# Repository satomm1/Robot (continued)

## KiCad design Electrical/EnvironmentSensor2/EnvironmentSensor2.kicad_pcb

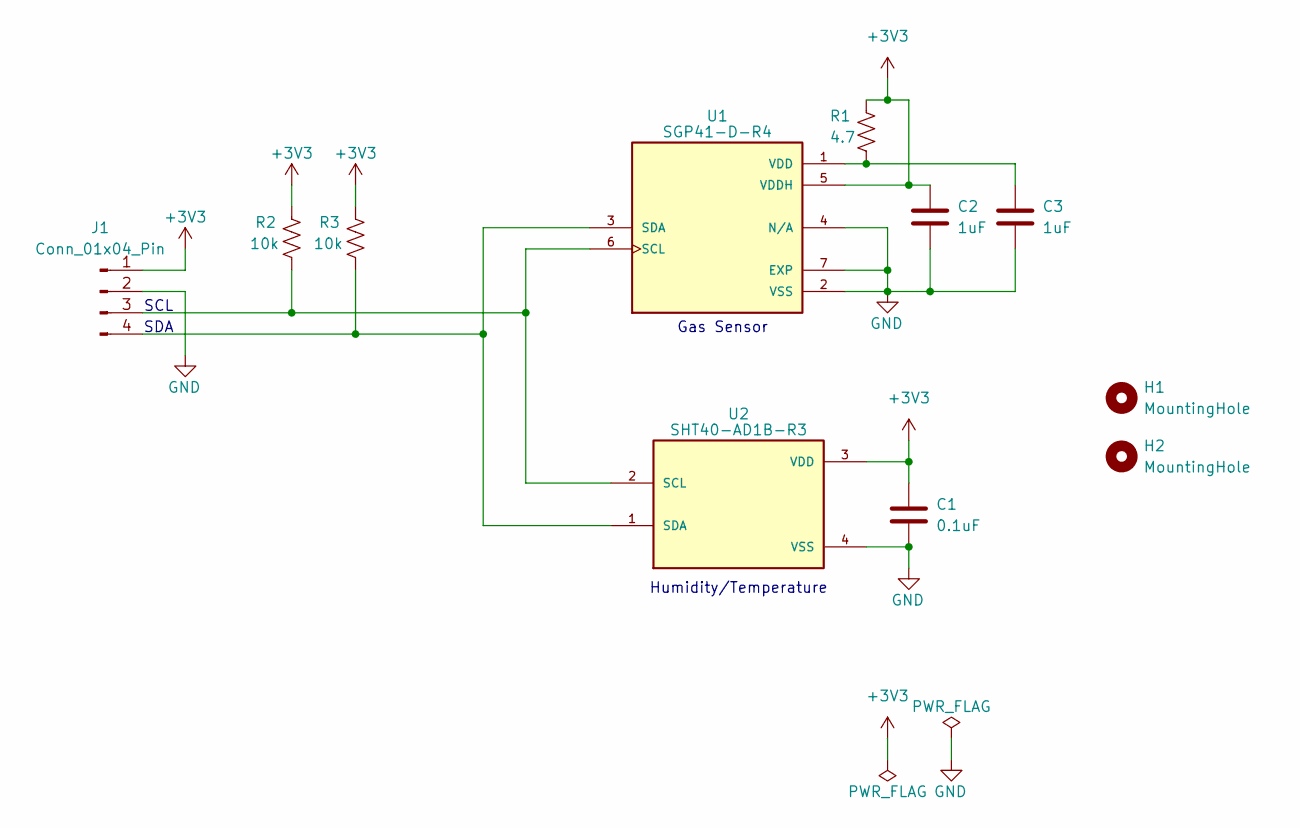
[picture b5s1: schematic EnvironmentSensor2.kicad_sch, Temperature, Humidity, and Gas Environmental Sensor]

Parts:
C1: 0.1uF; C_0805_2012Metric_Pad1.18x1.45mm_HandSolder; Mfr P/N CL21B104KBCNNNC
C2, C3: 1uF; C_0805_2012Metric_Pad1.18x1.45mm_HandSolder; Mfr P/N 1276-1066-1-ND
H1, H2: MountingHole; MountingHole_3.2mm_M3
J1: Conn_01x04_Pin; Molex_PicoBlade_53048-0410_1x04_P1.25mm_Horizontal; Mfr P/N 0530480410
R1: 4.7; R_0805_2012Metric_Pad1.20x1.40mm_HandSolder; Mfr P/N RC0805FR-074R7L
R2, R3: 10k; R_0805_2012Metric_Pad1.20x1.40mm_HandSolder; Mfr P/N RMCF0805FT10K0
U1: SGP41-D-R4; XDCR_SGP41-D-R4; Mfr P/N SGP41-D-R4
U2: SHT40-AD1B-R3; SHT4X; Mfr P/N SHT40-AD1B-R3

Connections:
+3V3: C1.1, C2.1, J1.1, R1.1, R2.1, R3.1, U1.5 (VDDH), U2.3 (VDD)
GND: C1.2, C2.2, C3.2, J1.2, U1.2 (VSS), U1.4 (N/A), U1.7 (EXP), U2.4 (VSS)
unnamed: J1.3, R2.2, U1.6 (SCL), U2.2 (SCL)
unnamed: J1.4, R3.2, U1.3 (SDA), U2.1 (SDA)
unnamed: C3.1, R1.2, U1.1 (VDD)

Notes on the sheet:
SDA
Gas Sensor
Humidity/Temperature
SCL

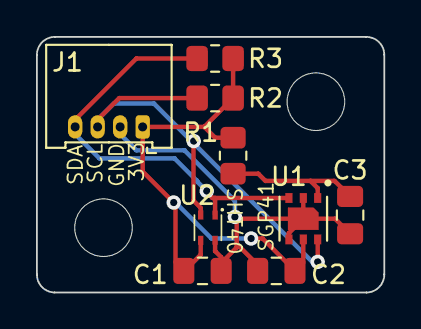
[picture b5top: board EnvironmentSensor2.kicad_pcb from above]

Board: 2 copper layers, 19.3 x 14.2 mm, 11 parts (0 on the bottom side), 5 nets.

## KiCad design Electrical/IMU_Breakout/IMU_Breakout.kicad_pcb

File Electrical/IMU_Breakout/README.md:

# 6-axis IMU

This directory contains the electrical schematic for a breakout board for the Bosch BMI323 6-axis IMU. This IMU provides a 16 bit digital triaxial accelerometer, a 16 bit digital triaxial gyroscope, and a 16 bit digital temperature sensor.

This breakout board is designed so that the IMU can be placed anywhere that is convenient.

## Soldering the IMU
This IMU is in a QFN package, which means the device should be reflow soldered. Alternatively, you can carefully apply solder to the PCB pads, put the IMU on top, and use a heat gun to solder the IMU.

## Pin directions
The header pins should be soldered on the bottom of the PCB:

## Installing the IMU
The assembly is meant to be installed on the robot with the IMU facing upwards. The positive X/Y/Z axes are designated on the board. The IMU should be connected via wire to the designated header on the main control board:

| IMU Breakout Pin | Main Control Board Connection |
|------------------|-------------------------------|
| 3V3              | 3.3V                          |
| GND              | GND                           |
| SCK              | SCK                           |
| CS               | CS                            |
| SDO              | SDI                           |
| SDI              | SDO                           |
| INT1             | INT1 (Currently Unused)       |
| INT2             | INT2 (Currently Unused)       |

The IMU connection on the main control board is indicated below:

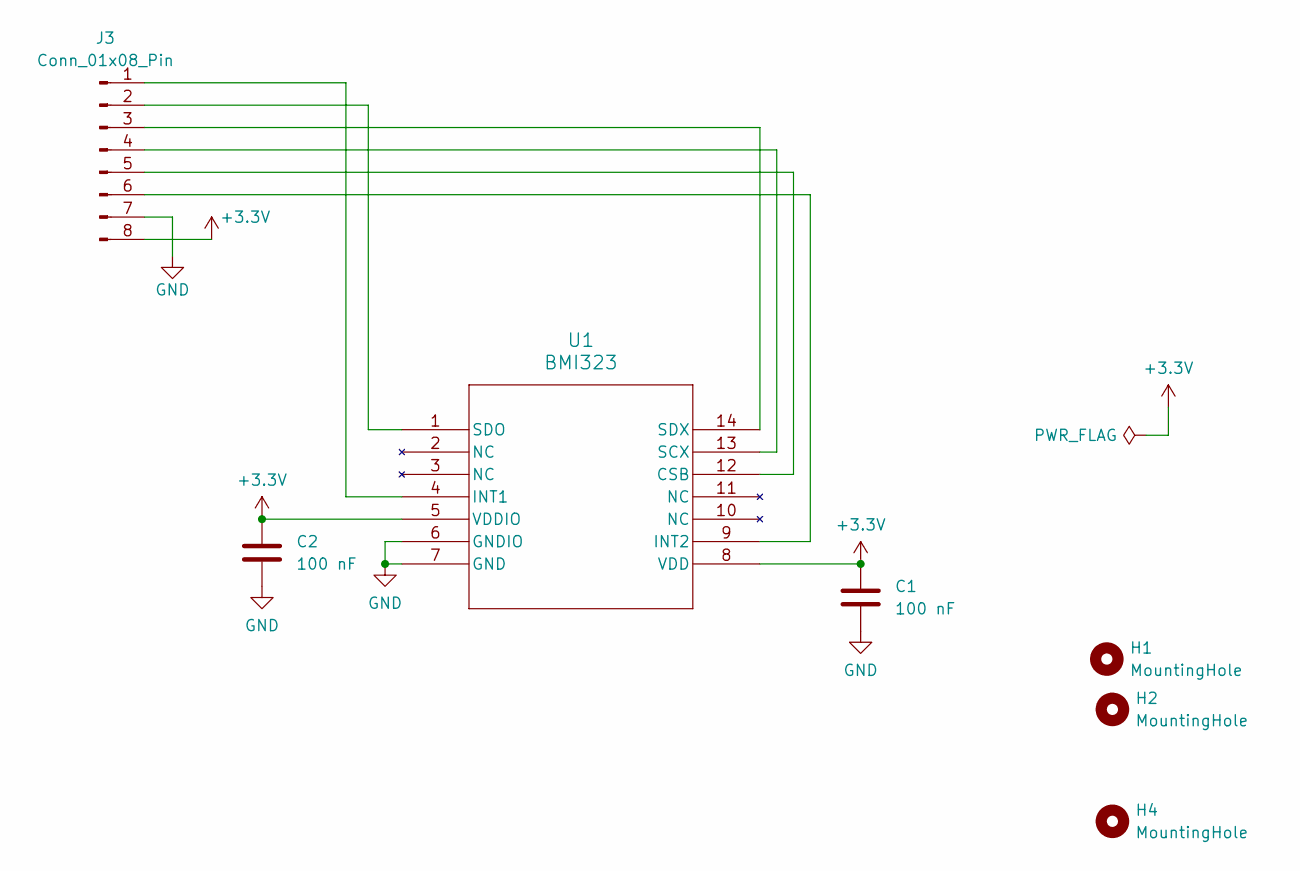
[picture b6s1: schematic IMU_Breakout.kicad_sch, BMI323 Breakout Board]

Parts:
C1, C2: 100 nF; C_0805_2012Metric_Pad1.18x1.45mm_HandSolder; Mfr P/N CL21B104KBCNNNC
H1, H2, H4: MountingHole; MountingHole_3.2mm_M3
J3: Conn_01x08_Pin; Molex_PicoBlade_53048-0810_1x08_P1.25mm_Horizontal; Mfr P/N 0530480810
U1: BMI323; BMI323_BOS-M; Mfr P/N BMI323

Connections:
+3.3V: C1.1, C2.1, J3.8, U1.5 (VDDIO), U1.8 (VDD)
GND: C1.2, C2.2, J3.7, U1.6 (GNDIO), U1.7 (GND)
unnamed: J3.1, U1.4 (INT1)
unnamed: J3.2, U1.1 (SDO)
unnamed: J3.3, U1.14 (SDX)
unnamed: J3.4, U1.13 (SCX)
unnamed: J3.5, U1.12 (CSB)
unnamed: J3.6, U1.9 (INT2)

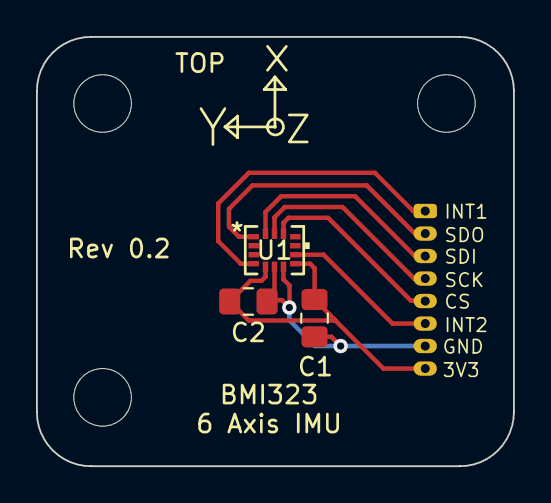
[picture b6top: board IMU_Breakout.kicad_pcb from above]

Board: 2 copper layers, 26.5 x 23.9 mm, 7 parts (1 on the bottom side), 8 nets.

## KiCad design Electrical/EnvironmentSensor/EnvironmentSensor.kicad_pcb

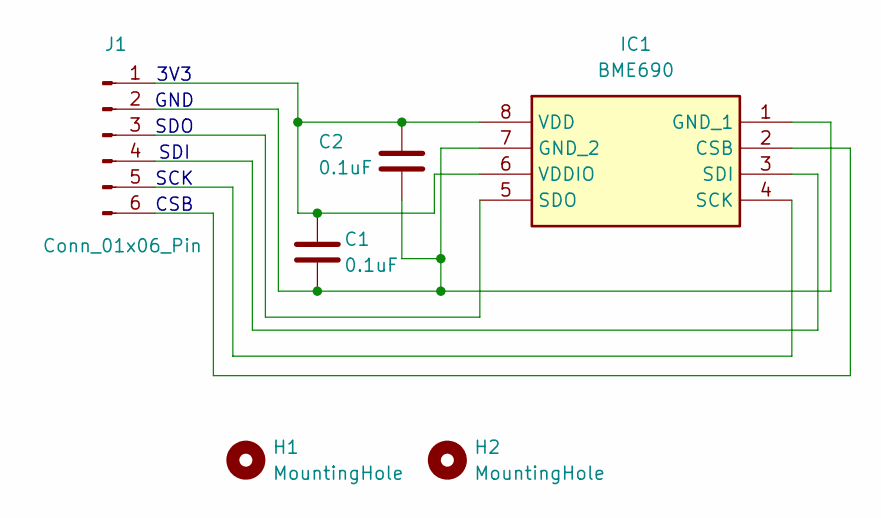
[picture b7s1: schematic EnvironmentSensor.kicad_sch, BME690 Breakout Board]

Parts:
C1, C2: 0.1uF; C_0805_2012Metric_Pad1.18x1.45mm_HandSolder; Mfr P/N CL21B104KBCNNNC
H1, H2: MountingHole; MountingHole_3.2mm_M3
IC1: BME690; Mouser Part Number 262-BME690
J1: Conn_01x06_Pin; Molex_PicoBlade_53048-0610_1x06_P1.25mm_Horizontal; Mfr P/N 0530480610

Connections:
unnamed: IC1.2 (CSB), J1.6
unnamed: C1.2, C2.2, IC1.1 (GND_1), IC1.7 (GND_2), J1.2
unnamed: IC1.4 (SCK), J1.5
unnamed: IC1.3 (SDI), J1.4
unnamed: IC1.5 (SDO), J1.3
unnamed: C1.1, C2.1, IC1.6 (VDDIO), IC1.8 (VDD), J1.1

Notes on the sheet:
GND
SDI
CSB
SDO
3V3
SCK

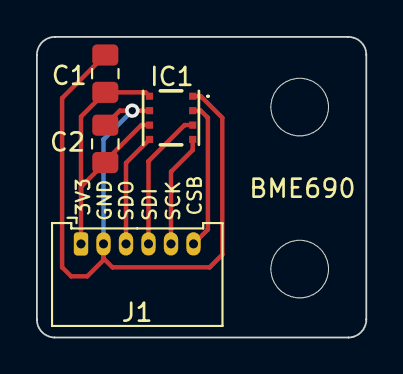
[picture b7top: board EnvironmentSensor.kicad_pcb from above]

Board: 2 copper layers, 18.3 x 16.7 mm, 6 parts (0 on the bottom side), 6 nets.

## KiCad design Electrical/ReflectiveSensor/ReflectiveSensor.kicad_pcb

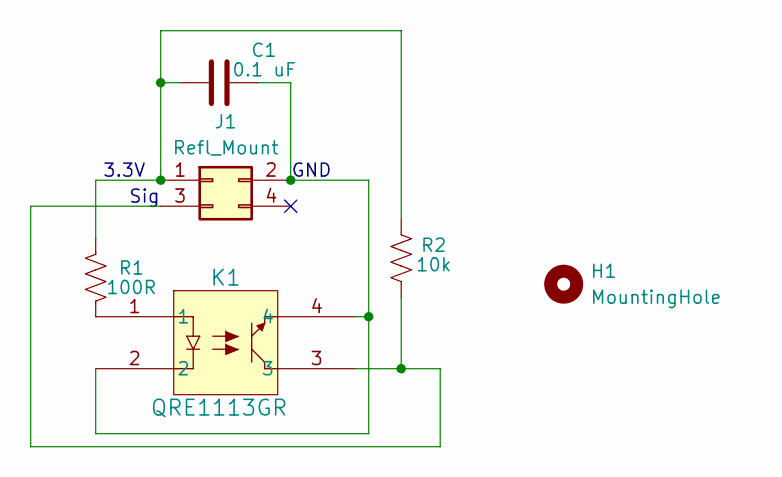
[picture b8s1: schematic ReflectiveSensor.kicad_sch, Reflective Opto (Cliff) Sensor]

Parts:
C1: 0.1 uF; C_0805_2012Metric_Pad1.18x1.45mm_HandSolder; Mfr P/N CL21B104KBCNNNC
H1: MountingHole; MountingHole_2.2mm_M2
J1: Refl_Mount; PinHeader_2x02_P2.54mm_Vertical
K1: QRE1113GR; ARUSM-313_100CY_FAS-M; Mfr P/N QRE1113GR
R1: 100R; R_0805_2012Metric_Pad1.20x1.40mm_HandSolder; Mfr P/N RMCF0805FT100R
R2: 10k; R_0805_2012Metric_Pad1.20x1.40mm_HandSolder; Mfr P/N RMCF0805FT10K0

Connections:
unnamed: C1.1, J1.1, R1.2, R2.2
unnamed: C1.2, J1.2, K1.2, K1.4
unnamed: J1.3, K1.3, R2.1
unnamed: K1.1, R1.1

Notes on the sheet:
GND
Sig
3.3V

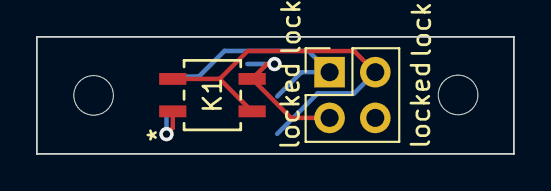
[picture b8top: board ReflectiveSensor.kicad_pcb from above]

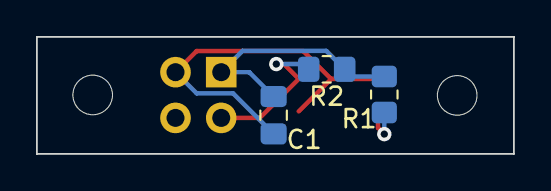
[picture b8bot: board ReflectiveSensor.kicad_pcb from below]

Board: 2 copper layers, 26.5 x 6.5 mm, 7 parts (3 on the bottom side), 4 nets.

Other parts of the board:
H2: MountingHole; MountingHole_2.2mm_M2

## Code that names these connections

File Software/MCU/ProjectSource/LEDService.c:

/****************************************************************************
 Module
   LEDService.c

 Revision
   1.0.1

 Description
   This is a file for implementing the LED service under the
   Gen2 Events and Services Framework.

 Notes

 History
 When           Who     What/Why
 -------------- ---     --------

****************************************************************************/
/*----------------------------- Include Files -----------------------------*/
/* include header files for this state machine as well as any machines at the
   next lower level in the hierarchy that are sub-machines to this machine
*/
#include "ES_Configure.h"
#include "ES_Framework.h"
#include "LEDService.h"

/*----------------------------- Module Defines ----------------------------*/

/*---------------------------- Module Functions ---------------------------*/
/* prototypes for private functions for this service.They should be functions
   relevant to the behavior of this service
*/

/*---------------------------- Module Variables ---------------------------*/
// with the introduction of Gen2, we need a module level Priority variable
static uint8_t MyPriority;

/*------------------------------ Module Code ------------------------------*/
/****************************************************************************
 Function
     InitLEDService

 Parameters
     uint8_t : the priorty of this service

 Returns
     bool, false if error in initialization, true otherwise

 Description
     Saves away the priority, and does any
     other required initialization for this service
****************************************************************************/
bool InitLEDService(uint8_t Priority)
{
  ES_Event_t ThisEvent;

  MyPriority = Priority;
  
  // Set LED pins to digital output
  TRISCCLR = _TRISC_TRISC12_MASK | _TRISC_TRISC15_MASK;
  TRISHCLR = _TRISH_TRISH4_MASK | _TRISH_TRISH5_MASK | _TRISH_TRISH6_MASK | _TRISH_TRISH7_MASK;
  
  ANSELHCLR = _ANSELH_ANSH4_MASK | _ANSELH_ANSH5_MASK | _ANSELH_ANSH6_MASK;
  
  // Start with all LEDs turned off
  LATHbits.LATH4 = 0; // LED2
  LATHbits.LATH5 = 0; // LED1
  LATHbits.LATH6 = 0; // LED4
  LATHbits.LATH7 = 0; // LED3
  LATCbits.LATC12 = 0; // LED6
  LATCbits.LATC15 = 0; // LED5
  
  // post the initial transition event
  ThisEvent.EventType = ES_INIT;
  if (ES_PostToService(MyPriority, ThisEvent) == true)
  {
    return true;
  }
  else
  {
    return false;
  }
}

/****************************************************************************
 Function
     PostLEDService

 Parameters
     EF_Event_t ThisEvent ,the event to post to the queue

 Returns
     bool false if the Enqueue operation failed, true otherwise

 Description
     Posts an event to this state machine's queue
****************************************************************************/
bool PostLEDService(ES_Event_t ThisEvent)
{
  return ES_PostToService(MyPriority, ThisEvent);
}

/****************************************************************************
 Function
    RunLEDService

 Parameters
   ES_Event_t : the event to process

 Returns
   ES_Event, ES_NO_EVENT if no error ES_ERROR otherwise

 Description
   Turns LEDs on or off
****************************************************************************/
ES_Event_t RunLEDService(ES_Event_t ThisEvent)
{
  ES_Event_t ReturnEvent;
  ReturnEvent.EventType = ES_NO_EVENT; // assume no errors
  
  switch (ThisEvent.EventType) {
      
      // Turn a LED on
      case EV_LED_ON:
      {
          // Event Parameter is the LED to turn on
          switch (ThisEvent.EventParam) {
              case 1:
              {
                  LATHbits.LATH5 = 1;
              }
              break;
              
              case 2:
              {
                  LATHbits.LATH4 = 1;
              }
              break;
              
              case 3:
              {
                  LATHbits.LATH7 = 1;
              }
              break;
              
              case 4:
              {
                  LATHbits.LATH6 = 1;
              }
              break;
              
              case 5:
              {
                  LATCbits.LATC15 = 1;
              }
              break;
              
              case 6:
              {
                  LATCbits.LATC12 = 1;
              }
              break;
              
              default:
                break;
          }
      }
      break;
      
      // Turn a LED off
      case EV_LED_OFF:
      {
          // Event Parameter is the LED to turn off
          switch (ThisEvent.EventParam) {
              case 1:
              {
                  LATHbits.LATH5 = 0;
              }
              break;
              
              case 2:
              {
                  LATHbits.LATH4 = 0;
              }
              break;
              
              case 3:
              {
                  LATHbits.LATH7 = 0;
              }
              break;
              
              case 4:
              {
                  LATHbits.LATH6 = 0;
              }
              break;
              
              case 5:
              {
                  LATCbits.LATC15 = 0;
              }
              break;
              
              case 6:
              {
                  LATCbits.LATC12 = 0;
              }
              break;
              
              default:
                break;
          }
      }
      break;
      
      default:
        break;
  }
    
  return ReturnEvent;
}

/***************************************************************************
 private functions
 ***************************************************************************/

/*------------------------------- Footnotes -------------------------------*/
/*------------------------------ End of file ------------------------------*/

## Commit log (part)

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2023-11-08 Add initial directories and READMEs
2023-11-08 Update KiCAD format
2023-11-11 Add the majority of the electronics
2023-11-13 Begin layout of pcb
2023-11-16 First Pass at the routing
2023-11-25 Some finishing touches to the board
2023-11-25 Add a bom and initial mechanical drawings
2023-11-25 Finalize Reflective Opto Sensor
2023-11-26 Add some final touches
2023-11-27 Resize the reflective sensor
2023-11-27 Add updated robot design
2023-11-29 Add Robot Summary Document
2023-11-30 Finish final board design for Rev 0.1 Main board and reflective Sensor. Created Gerbers.
2023-12-01 Add initial PIC32 Framework Code
2023-12-20 Add starter code for the IMU and Motor Control state machines
2023-12-28 Add some code for communicating between ros and MCU
2023-12-29 Add button debouncers and add more motor control
2024-01-08 Dead reckoning and IMU
2024-01-09 Sort out some of the details for jetson-MCU comms and do some more motor code
2024-01-10 Fully align ROS python code with MCU for spi transfer
2024-01-10 Add a service to turn LEDs on or off
2024-01-11 Modify the spi comms file
2024-01-11 Made a comment that we may need a small resistor to draw some current from battery to keep on
2024-01-19 updated model
2024-01-20 Add bom for reflective sensor pcb
2024-01-20 Add backups
2024-01-23 Backups
2024-01-23 Add updates
2024-01-24 Begin the debugging process. Know LEDs and USB-UART are working here
2024-01-26 Get most services at least functioning without crashing
2024-01-26 Confirm button debouncers/state machines work
2024-01-26 Add code for basic motor testing
2024-01-28 Get PI control mostly working
2024-01-29 Updates to robot upper level design
2024-01-29 Get SPI between jetson and mcu figured out
2024-01-31 Implement Jetson comm functionality for dead reckoning and position
2024-02-02 Just making more progress...
2024-02-02 Add IMU breakout board design
2024-02-02 Made V0.2 revisions to Main Board
2024-02-05 Directly write to SPI2BUF instead of passing it as an argument
2024-02-06 Change limits on maximum velocities
2024-02-07 Change molex+terminal block to just 6 position molex for the motor/encoder terminal
2024-02-07 Center the IMU
2024-02-08 Update dead reckoning update to occur at 50 Hz rate, also update base width of robot
2024-02-09 just some backups
2024-02-14 Change some spi stuff with jetson, probably will need to revert
2024-02-14 Revert "Change some spi stuff with jetson, probably will need to revert"
    This reverts commit 06b93681a91bff43f5faf43f78ca409b5d33d08e.
    Revert back to PI control instead of PID
2024-02-14 Change to PID control
2024-02-14 Allocate 16 bytes for the receiveBuffer-- May have been causing the problem of data getting misaligned with jetson
2024-03-08 MPLAB xml file
2024-03-10 Finalize IMU Breakout board
2024-03-10 Finalize rev 0.2
2024-03-10 Add V0.2 to archive
2024-03-11 Dead reckoning use exact formula, increase rate at which dead reckoning is calculated
2024-03-11 further reduce update time for dead reckoning calcs
2024-03-21 Add file for testing IMU
2024-03-21 Begin adding new initialization code for BMI IMU
2024-03-23 Add code for testing ADC, should be good now just need to debug
2024-04-02 Edit imu code
2024-04-02 Finalize code for setting up IMU and verifying soldering is correct
2024-04-07 Get code for IMU working
2024-04-08 Get ADC test code working
2024-04-08 Integrate ADC/Reflect service with Jetson messaging
2024-04-10 Add new details to the bringup document
2024-04-10 Add updated components
2024-04-22 Add minimally working docker files for running Kafka/Zookeeper
2024-04-22 Make some useful comments in a README
2024-05-03 Add IMU capability for REV 0.1 board
2024-05-03 Finish debugging new IMU setup
2024-05-06 Add functionality to easily switch between the different encoders
2024-05-24 Add ability to query the fault status of the two motor drivers
2024-07-26 Estimate orienation using Madgwick filter from IMU
2024-07-26 Give document for docker container setup
2024-08-16 Begin adding code fo rEEPORM and RL
2024-08-16 Add some bringup instructions
2024-08-20 Tune parameters in Motor and fix small issues
2024-10-28 Add button data to info sent to Jetson
2024-12-19 Update instruction sheets
2024-12-19 First attempt at EEPROM writing
2024-12-19 Add write disable capability
2024-12-19 Get write enable/disable tested and working
2025-01-17 Make it easy to turn off data logging for RL
2025-04-04 Add updates to docker container setup
2025-04-04 Comment out IMU stuff so isn't being run
2025-04-04 Add updates/improvements to EEPROM implementation
2025-05-14 A private.xml file
2025-05-15 Add gerber files
2025-05-15 Add more README
2025-05-16 Add stl and dxf files
2025-05-16 Add to README
2025-05-17 Add reference sizes for 3d prints and laser cuts
2025-05-17 Update README with detailed microcontroller programming instructions and add setup guide for Nvidia Jetson; include image for programming button
2025-05-17 Update the jetson bringup directions
2025-05-17 Update mplab file
2025-05-17 Remove old ROS Readme
2025-05-19 Fix SPI3 and make visual improvements
2025-05-19 Add updated gerbers
2025-05-20 clarify jetson io file
2025-05-22 Add updates to bringup instructions
2025-05-22 Provide more setup information
2025-05-22 Update documentation for improved setup instructions
2025-05-22 Add instructions for gui setup
2025-05-26 Add SetPosition function to MotorSM for position updates
2025-05-26 Use activation confirmation message to set odometry position (x/y/theta)
2025-05-26 Some configuration files
2025-05-26 Remove old/unused code
2025-05-27 Add readme for PCB bring up
2025-05-27 Add mic setup instructions
2025-05-27 Give Jetson I2S Pins
2025-05-28 Add ability to auto clone all the repos
2025-05-29 IMU test can now provide roll/pitch
2025-05-29 Add IMU code to mainboard code with mahony filter
2025-05-31 Update some parts
2025-06-03 Finalize V0.3 of main board
2025-06-03 Change timer 1 start/stops to faster calls
2025-06-03 Change control period based on motor
2025-06-06 Add 3 pin male to BOM
2025-06-06 Add inventor implementation
2025-06-09 Account for pitch/roll in odometry
2025-06-09 CAD updates
2025-06-09 Add code to ignore wrong RPM Measurements
2025-06-09 Update the status LED to common anode
2025-06-09 Move wheel distance to es_configure
2025-06-11 Update the datasheets
2025-06-11 Finalize the PCBs
2025-06-13 Make more cad files
2025-06-13 Drive shaft and wheels spacer
2025-06-16 Add more files
2025-06-18 Indicate the parts that can be 3D printed no matter the materials purchased
2025-06-18 Add more instructions/pictures
2025-06-18 Add markdown for 3d printed parts
2025-06-18 Add details on what components don't depend on materials
2025-06-24 Add note about heat set inserts
2025-06-27 Update the dxf files
2025-06-27 updated config files
2025-06-27 Add more details and add a Jetson Section
2025-06-27 Move word files to README
2025-06-27 fix typos
2025-06-27 Add display instructions
2025-07-01 Update the layer 1 for new ball caster location
2025-07-05 Do not allow too large of measured V or w
2025-07-05 ALlow for PCB REV 3 to be chosen
2025-07-11 Update instructions for starting gemini endpoint
2025-07-14 Update files
2025-07-16 Add svg files for the laser cutter
2025-07-17 Add caster spacers
2025-07-21 update level6
2025-07-21 fix level 3 hole size for standoffs
2025-07-25 Remove while loop in ISR
2025-07-25 Add keystroke for odometry estimates
2025-08-06 Update the connection for IMU breakout board
2025-08-06 Add environment sensor
2025-08-06 add stl for full jetson holder
2025-08-06 add updated gerber zips
2025-08-06 Use imu only if setup is verified
2025-08-06 Change some connections to picoblade, add env sensor connector
2025-08-07 Add link to instruction guide webpage
2025-08-08 Add environmental sensor which uses separate temp/hum and gas sensors (more open source)
2025-08-15 Finalize updated schematics
2025-08-15 Make a robot assembly with all round layers
2025-10-01 Add a case for the environmental sensor
2025-10-01 Begin implementation of environmental sensor code
2025-10-14 Get gas/temp/humidty sensor code mostly up and running
2025-10-14 Add updated cad files
2025-10-15 Revise README with spidev module loading instructions
    Updated instructions for loading the spidev module and reordering steps for clarity.
2025-10-15 Update Jetson connection instructions in README
    Clarified Jetson connection details and added note about twisted pair wire.
2025-10-19 Fully process temp/humidity, air quality data and send to jetson
2025-10-19 Get environment sensor code fully integrated
2025-10-19 Fix SPI reception handling to prevent message loss when data is delayed
2025-10-21 Finalize the production ready code
2025-10-23 Change polarity of RightRotations and LeftRotations for PCB_REV > 2
2025-11-09 Move wheel radius to es_configure file
2026-05-16 Specify the dead reckoning frequency/time better and set to 50 Hz
2026-05-16 Update the control timer frequency to 1000 (previously missing factor of 2)
2026-05-16 Add helper function for sending EEPROM read or write instructions
2026-05-16 Update SPI mode settings
2026-05-16 Add WriteByteAtAddressEEPROM function to handle byte writing at specific addresses
2026-05-17 Fix indexing in messsage to send
2026-05-17 Improve signed data conversion
2026-05-18 updated mechanical designs
2026-05-18 misc electrical updates
2026-05-20 Use different PID gains when turning only and add slew limits
2026-05-21 Add test files for downloading automatic start up scripts
2026-05-21 Update robot_env.sh to include comments for user configuration
2026-05-21 Add the startup script
2026-05-21 Update startup script to suppress logging and allow status checks
2026-05-22 Enhance IMU state machine: add IMUInitFailed state, improve initialization logic, and implement SPI data handling functions
2026-05-22 Enhance IMU state machine: add IMURecovering state, implement recovery logic, and improve error handling
2026-05-23 Refactor MotorSM: update dead reckoning period, adjust control period, and enhance encoder handling for improved accuracy
2026-05-23 Baseline Improve Motor Control/Odometry
2026-05-24 update control period, enhance encoder handling, and improve RPM calculation logic
2026-05-24 Make clear pid parameters are floats
2026-05-24 Fix small bugs and add hysteris for rpm calculation in motor control
2026-05-24 Increase encoder resolution for motor_type==2
2026-05-24 Add robot_car variable to include car argument in the startup_script
2026-05-24 Add GetRobotYawRate function to retrieve robot yaw rate from Gyro Z
2026-05-25 Enhance startup_script to support social and multi-agent launch configurations
2026-05-28 Create automated roaming wifi setup script
2026-05-28 Update startup script to allow software updates remotely
2026-06-01 Update startup script repo
2026-06-01 Add Jetson host service and installation scripts for Docker control
2026-06-01 Update Gemini container setup instructions to pull from GHCR
2026-06-01 remove pid=host
2026-06-19 Add mattbot_capture to Jetson repo clone setup.
    Include the new capture package in clone_repos.sh and document it in the Jetson README so fresh workspaces pull it with the other ROS packages.
2026-06-21 Update Motor to allow rotated configuration for car (default) and add nan protections in pitch/roll
2026-06-21 Update compiler
2026-06-21 Add path_planning repository to clone_repos.sh
2026-06-22 Add Gemini container support: implement environment file checks for API_KEY
2026-06-23 Update host service to allow map syncing
2026-06-27 Improve bringup message handling and improve SPI RX framing
2026-06-27 Enable backup motor brownout to stop motors and reset jetson connection
